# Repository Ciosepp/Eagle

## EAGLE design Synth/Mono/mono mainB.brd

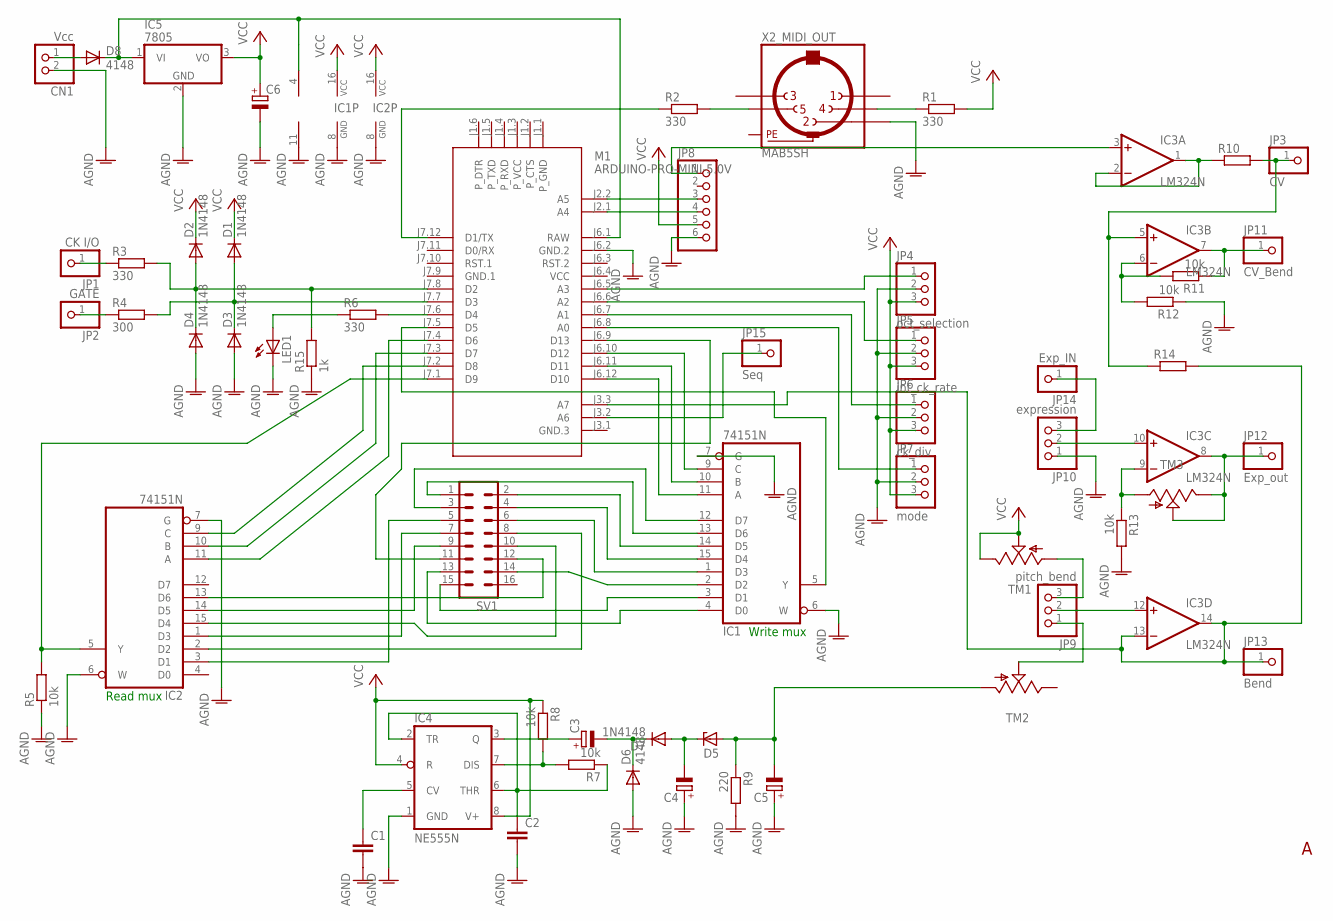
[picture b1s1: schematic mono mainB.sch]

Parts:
C1, C2: C-EU050-025X075; C050-025X075
C3, C4, C5, C6: CPOL-EUE5-8.5; E5-8,5
CN1: Vcc; JST-PH-2-THM
D1, D2, D3, D4, D7: 1N4148; DO35-7
D5: ZENER-DIODEZD-7.5; ZDIO-7.5
D6, D8: 4148; DO35-7
IC1, IC2: 74151N; DIL16
IC3: LM324N; DIL14
IC4: NE555N; DIL08-ROUND
IC5: 7805; TO220V
JP1: CK I/O; 1X01
JP2: GATE; 1X01
JP3: CV; 1X01
JP4: oct_selection; 1X03
JP5: int_ck_rate; 1X03
JP6: ck_div; 1X03
JP7: mode; 1X03
JP8: PINHD-1X6; 1X06
JP9: pitch_bend; 1X03
JP10: expression; 1X03
JP11: CV_Bend; 1X01
JP12: Exp_out; 1X01
JP13: Bend; 1X01
JP14: Exp_IN; 1X01
JP15: Seq; 1X01
LED1: LED5MM
M1: ARDUINO-PRO-MINI-5.0V; ARDUINO-PRO-MINI
R1: 330; 0204V
R2, R3: 330; 0204/7
R4: 300; 0204/7
R5: 10k; 0204/7
R6: 330; 0207/10
R7, R8, R11: 10k; 0204V
R9: 220; 0204V
R10, R14: R0204/7; 0204/7
R12, R13: 10k; 0207/10
R15: 1k; 0204/7
SV1: MA08-2
TM1, TM2, TM3: TRIM; 6MM
X2_MIDI_OUT: MAB5SH

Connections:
AGND: C1.2, C2.2, C4.+, C5.+, C6.-, CN1.2 (1), D3.A, D4.A, D6.A, IC1.6 (W), IC1.7 (G), IC1.8 (GND), IC2.6 (W), IC2.7 (G), IC2.8 (GND), IC3.11 (V-), IC4.1 (GND), IC5.2 (GND), JP4.2, JP5.2, JP6.2, JP7.2, JP8.6, JP10.1, LED1.K (C), M1.J6.2 (GND.2), R5.1, R9.2, R12.1, R13.2, R15.1, X2_MIDI_OUT.2
GND.1: M1.J7.9 (GND.1)
unnamed: IC1.12 (D7), SV1.3
unnamed: IC1.13 (D6), SV1.1
unnamed: IC1.14 (D5), SV1.2
unnamed: IC1.15 (D4), SV1.4
unnamed: IC1.1 (D3), SV1.6
unnamed: IC1.4 (D0), SV1.13
unnamed: IC1.2 (D2), SV1.14
unnamed: IC1.3 (D1), SV1.15
unnamed: IC2.13 (D6), SV1.12
unnamed: IC2.14 (D5), SV1.9
unnamed: IC2.15 (D4), SV1.10
unnamed: IC2.1 (D3), SV1.7
unnamed: IC2.2 (D2), SV1.8
unnamed: JP1.1, R3.1
unnamed: IC1.11 (A), M1.J6.12 (D10)
unnamed: IC1.10 (B), M1.J6.11 (D11)
unnamed: M1.J7.12 (D1/TX), R2.1
unnamed: IC2.3 (D1), SV1.5
unnamed: JP8.3, M1.J2.2 (A5)
unnamed: D2.A, D4.C, M1.J7.8 (D2), R3.2, R15.2
unnamed: D1.A, D3.C, M1.J7.7 (D3), R4.2
unnamed: IC2.5 (Y), M1.J7.1 (D9), R5.2
unnamed: IC1.5 (Y), M1.J7.5 (D5)
unnamed: JP6.1, M1.J6.7 (A1)
unnamed: JP5.1, M1.J6.6 (A2)
unnamed: JP2.1, R4.1
unnamed: JP8.4, M1.J2.1 (A4)
unnamed: R2.2, X2_MIDI_OUT.5
unnamed: R1.1, X2_MIDI_OUT.4
unnamed: IC3.9 (-IN), R13.1, TM3.A
unnamed: JP4.1, M1.J6.5 (A3)
unnamed: IC2.9 (C), M1.J7.2 (D8)
unnamed: IC2.10 (B), M1.J7.3 (D7)
unnamed: IC2.11 (A), M1.J7.4 (D6)
unnamed: LED1.A, R6.1
unnamed: M1.J7.6 (D4), R6.2
unnamed: IC4.7 (DIS), R7.2, R8.2
unnamed: C2.1, IC4.2 (TR), IC4.6 (THR), R7.1
unnamed: C1.1, IC4.5 (CV)
unnamed: IC3.1 (OUT), IC3.2 (-IN), R10.1
unnamed: C3.+, IC4.3 (Q)
unnamed: C3.-, D6.C, D7.C
unnamed: C4.-, D5.C, D7.A
unnamed: C5.-, D5.A, R9.1, TM2.A
unnamed: IC3.12 (+IN), JP9.2
unnamed: IC3.13 (-IN), IC3.14 (OUT), JP13.1, M1.J3.3 (A7), R14.2
unnamed: JP9.3, TM1.A
unnamed: IC3.10 (+IN), JP10.2
unnamed: IC3.8 (OUT), JP12.1, TM3.E, TM3.S
unnamed: CN1.1 (2), D8.A
unnamed: JP9.1, TM2.S
unnamed: IC3.6 (-IN), R11.2, R12.2
unnamed: IC3.7 (OUT), JP11.1, R11.1
unnamed: D8.C, IC3.4 (V+), IC5.1 (VI), M1.J6.1 (RAW)
unnamed: IC1.9 (C), M1.J6.10 (D12)
unnamed: IC3.3 (+IN), JP8.1
unnamed: IC3.5 (+IN), JP3.1, R10.2, R14.1
unnamed: JP10.3, JP14.1
unnamed: M1.J6.9 (D13), SV1.11
unnamed: JP7.1, M1.J6.8 (A0)
unnamed: JP15.1, M1.J3.2 (A6)
PE: X2_MIDI_OUT.PE, X2_MIDI_OUT.PE@ (PE)
VCC: C6.+, D1.C, D2.C, IC1.16 (VCC), IC2.16 (VCC), IC4.4 (R), IC4.8 (V+), IC5.3 (VO), JP4.3, JP5.3, JP6.3, JP7.3, JP8.5, M1.J6.4 (VCC), R1.2, R8.1, TM1.E, TM1.S

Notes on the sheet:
Read mux
Write mux

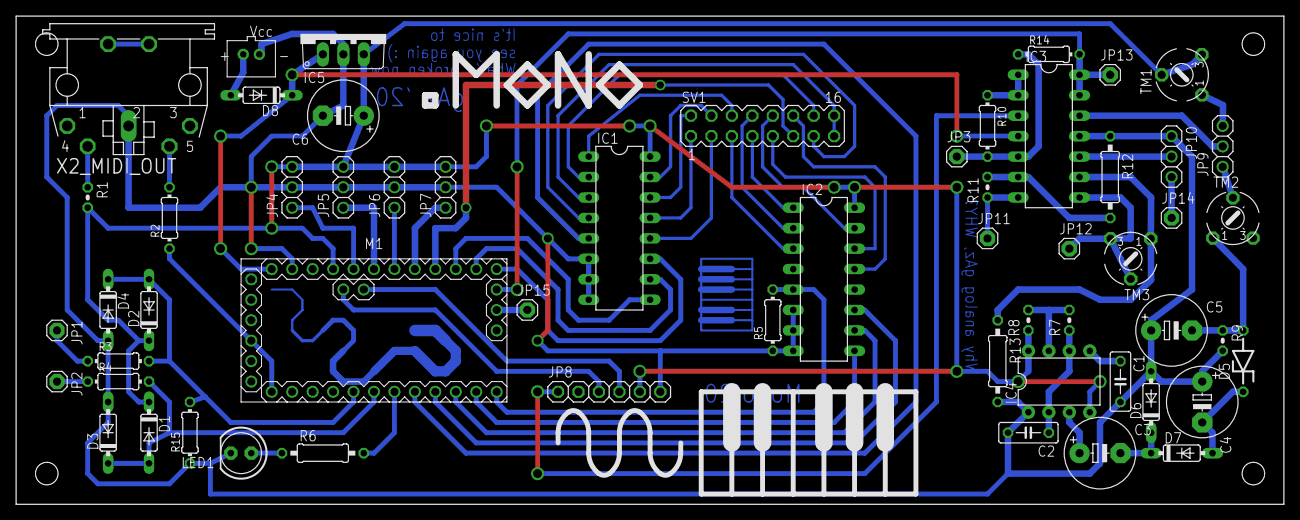
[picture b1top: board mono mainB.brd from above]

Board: 2 copper layers, 157.5 x 60.6 mm, 57 parts (0 on the bottom side), 64 nets.

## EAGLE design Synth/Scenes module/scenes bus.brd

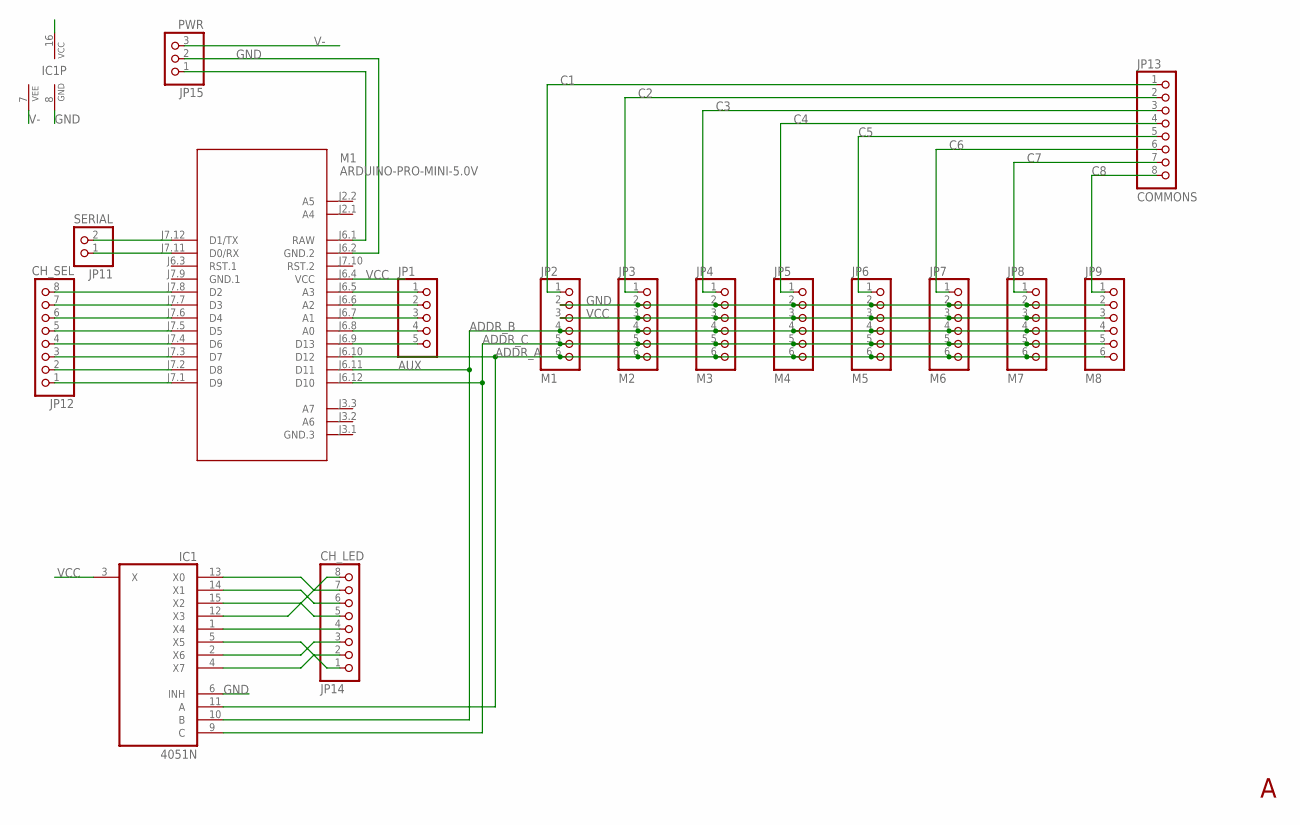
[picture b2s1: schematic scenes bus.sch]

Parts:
IC1: 4051N; DIL16
JP1: AUX; 1X05
JP2: M1; 1X06
JP3: M2; 1X06
JP4: M3; 1X06
JP5: M4; 1X06
JP6: M5; 1X06
JP7: M6; 1X06
JP8: M7; 1X06
JP9: M8; 1X06
JP11: SERIAL; 1X02
JP12: CH_SEL; 1X08
JP13: COMMONS; 1X08
JP14: CH_LED; 1X08
JP15: PWR; 1X03
M1: ARDUINO-PRO-MINI-5.0V; ARDUINO-PRO-MINI#NP

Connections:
ADDR_A: IC1.11 (A), JP2.6, JP3.6, JP4.6, JP5.6, JP6.6, JP7.6, JP8.6, JP9.6, M1.J6.10 (D12)
ADDR_B: IC1.10 (B), JP2.4, JP3.4, JP4.4, JP5.4, JP6.4, JP7.4, JP8.4, JP9.4, M1.J6.11 (D11)
ADDR_C: IC1.9 (C), JP2.5, JP3.5, JP4.5, JP5.5, JP6.5, JP7.5, JP8.5, JP9.5, M1.J6.12 (D10)
C1: JP2.1, JP13.1
C2: JP3.1, JP13.2
C3: JP4.1, JP13.3
C4: JP5.1, JP13.4
C5: JP6.1, JP13.5
C6: JP7.1, JP13.6
C7: JP8.1, JP13.7
C8: JP9.1, JP13.8
GND: IC1.6 (INH), IC1.8 (GND), JP2.2, JP3.2, JP4.2, JP5.2, JP6.2, JP7.2, JP8.2, JP9.2, JP15.2, M1.J6.2 (GND.2)
GND.1: M1.J7.9 (GND.1)
unnamed: JP1.1, M1.J6.5 (A3)
unnamed: JP1.2, M1.J6.6 (A2)
unnamed: JP1.3, M1.J6.7 (A1)
unnamed: JP1.4, M1.J6.8 (A0)
unnamed: JP1.5, M1.J6.9 (D13)
unnamed: JP12.1, M1.J7.1 (D9)
unnamed: JP12.2, M1.J7.2 (D8)
unnamed: JP12.3, M1.J7.3 (D7)
unnamed: JP12.4, M1.J7.4 (D6)
unnamed: JP12.5, M1.J7.5 (D5)
unnamed: JP12.6, M1.J7.6 (D4)
unnamed: JP12.7, M1.J7.7 (D3)
unnamed: JP12.8, M1.J7.8 (D2)
unnamed: IC1.1 (X4), JP14.4
unnamed: IC1.2 (X6), JP14.3
unnamed: JP11.2, M1.J7.12 (D1/TX)
unnamed: JP11.1, M1.J7.11 (D0/RX)
unnamed: IC1.4 (X7), JP14.2
unnamed: IC1.5 (X5), JP14.1
unnamed: JP15.1, M1.J6.1 (RAW)
unnamed: IC1.15 (X2), JP14.5
unnamed: IC1.14 (X1), JP14.6
unnamed: IC1.13 (X0), JP14.7
unnamed: IC1.12 (X3), JP14.8
V-: IC1.7 (VEE), JP15.3
VCC: IC1.3 (X), IC1.16 (VCC), JP2.3, JP3.3, JP4.3, JP5.3, JP6.3, JP7.3, JP8.3, JP9.3, M1.J6.4 (VCC)

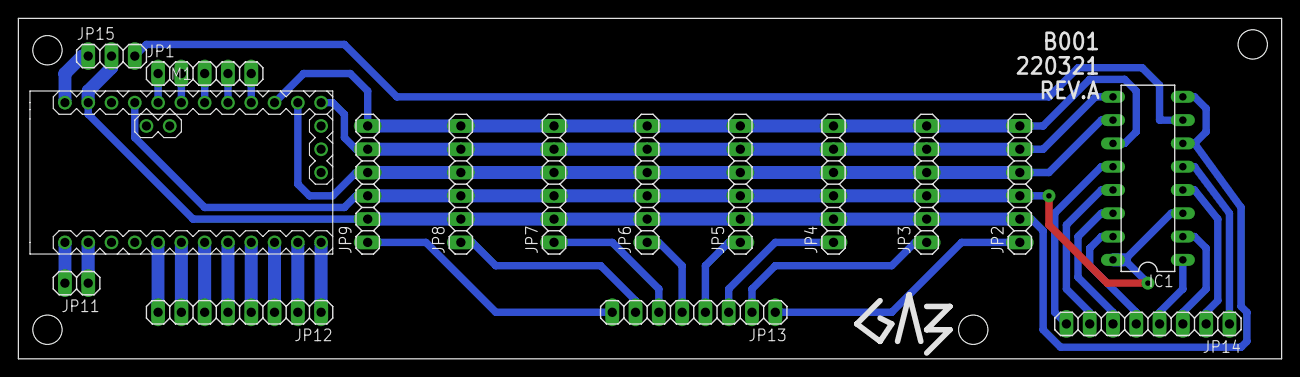
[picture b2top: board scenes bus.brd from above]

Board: 2 copper layers, 137.8 x 37.1 mm, 16 parts (0 on the bottom side), 38 nets.

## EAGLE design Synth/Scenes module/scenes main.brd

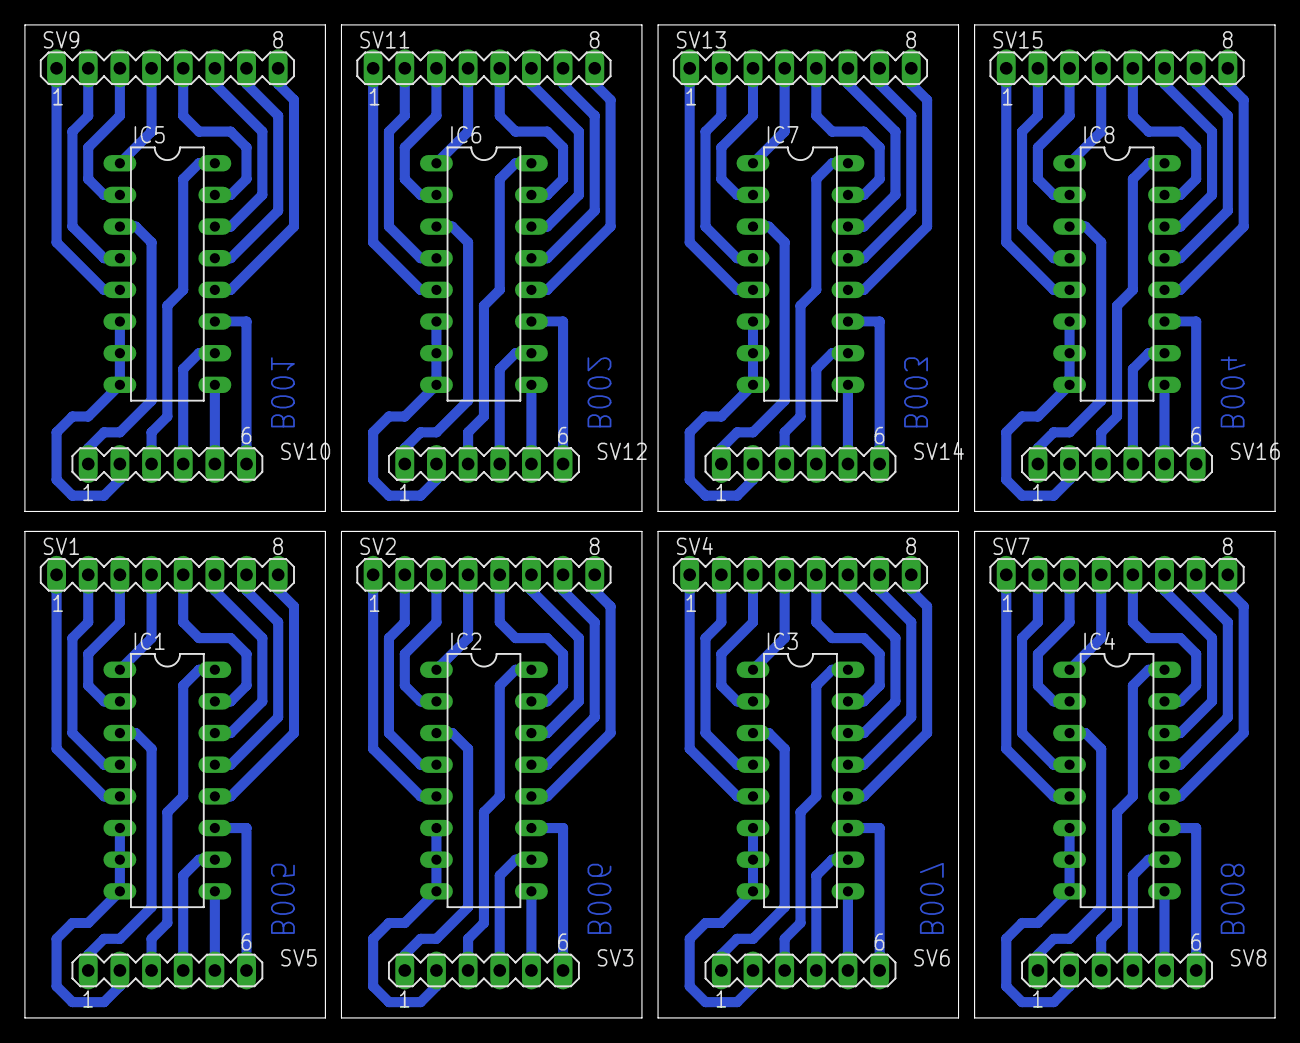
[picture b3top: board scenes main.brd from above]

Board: 2 copper layers, 100.3 x 79.7 mm, 24 parts (0 on the bottom side), 112 nets.

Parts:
IC1, IC2, IC3, IC4, IC5, IC6, IC7, IC8: 4051N; DIL16
SV1, SV2, SV4, SV7, SV9, SV11, SV13, SV15: MA08-1
SV3, SV5, SV6, SV8, SV10, SV12, SV14, SV16: MA06-1

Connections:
GND: IC1.6, IC1.8, SV5.2
GND1: IC2.6, IC2.8, SV3.2
GND2: IC3.6, IC3.8, SV6.2
GND3: IC4.6, IC4.8, SV8.2
GND4: IC5.6, IC5.8, SV10.2
GND5: IC6.6, IC6.8, SV12.2
GND6: IC7.6, IC7.8, SV14.2
GND7: IC8.6, IC8.8, SV16.2
unnamed: IC1.1, SV1.4
unnamed: IC1.2, SV1.3
unnamed: IC1.4, SV1.2
unnamed: IC1.5, SV1.1
unnamed: IC1.15, SV1.5
unnamed: IC1.14, SV1.6
unnamed: IC1.13, SV1.7
unnamed: IC1.12, SV1.8
unnamed: IC1.9, SV5.5
unnamed: IC1.10, SV5.4
unnamed: IC1.11, SV5.6
unnamed: IC2.1, SV2.4
unnamed: IC2.2, SV2.3
unnamed: IC2.4, SV2.2
unnamed: IC2.5, SV2.1
unnamed: IC2.15, SV2.5
unnamed: IC2.14, SV2.6
unnamed: IC2.13, SV2.7
unnamed: IC2.12, SV2.8
unnamed: IC2.3, SV3.1
unnamed: IC2.9, SV3.5
unnamed: IC2.10, SV3.4
unnamed: IC2.11, SV3.6
unnamed: IC3.1, SV4.4
unnamed: IC3.2, SV4.3
unnamed: IC3.4, SV4.2
unnamed: IC3.5, SV4.1
unnamed: IC3.15, SV4.5
unnamed: IC3.14, SV4.6
unnamed: IC3.13, SV4.7
unnamed: IC3.12, SV4.8
unnamed: IC3.3, SV6.1
unnamed: IC3.9, SV6.5
unnamed: IC3.10, SV6.4
unnamed: IC3.11, SV6.6
unnamed: IC4.1, SV7.4
unnamed: IC4.2, SV7.3
unnamed: IC4.4, SV7.2
unnamed: IC4.5, SV7.1
unnamed: IC4.15, SV7.5
unnamed: IC4.14, SV7.6
unnamed: IC4.13, SV7.7
unnamed: IC4.12, SV7.8
unnamed: IC4.3, SV8.1
unnamed: IC4.9, SV8.5
unnamed: IC4.10, SV8.4
unnamed: IC4.11, SV8.6
unnamed: IC5.1, SV9.4
unnamed: IC5.2, SV9.3
unnamed: IC5.4, SV9.2
unnamed: IC5.5, SV9.1
unnamed: IC5.15, SV9.5
unnamed: IC5.14, SV9.6
unnamed: IC5.13, SV9.7
unnamed: IC5.12, SV9.8
unnamed: IC5.3, SV10.1
unnamed: IC5.9, SV10.5
unnamed: IC5.10, SV10.4
unnamed: IC5.11, SV10.6
unnamed: IC6.1, SV11.4
unnamed: IC6.2, SV11.3
unnamed: IC6.4, SV11.2
unnamed: IC6.5, SV11.1
unnamed: IC6.15, SV11.5
unnamed: IC6.14, SV11.6
unnamed: IC6.13, SV11.7
unnamed: IC6.12, SV11.8
unnamed: IC6.3, SV12.1
unnamed: IC6.9, SV12.5
unnamed: IC6.10, SV12.4
unnamed: IC6.11, SV12.6
unnamed: IC7.1, SV13.4
unnamed: IC7.2, SV13.3
unnamed: IC7.4, SV13.2
unnamed: IC1.3, SV5.1
unnamed: IC7.5, SV13.1
unnamed: IC7.15, SV13.5
unnamed: IC7.14, SV13.6
unnamed: IC7.13, SV13.7
unnamed: IC7.12, SV13.8
unnamed: IC7.3, SV14.1
unnamed: IC7.9, SV14.5
unnamed: IC7.10, SV14.4
unnamed: IC7.11, SV14.6
unnamed: IC8.1, SV15.4
unnamed: IC8.2, SV15.3
unnamed: IC8.4, SV15.2
unnamed: IC8.5, SV15.1
unnamed: IC8.15, SV15.5
unnamed: IC8.14, SV15.6
unnamed: IC8.13, SV15.7
unnamed: IC8.12, SV15.8
unnamed: IC8.3, SV16.1
unnamed: IC8.9, SV16.5
unnamed: IC8.10, SV16.4
unnamed: IC8.11, SV16.6
VCC: IC1.16, SV5.3
VCC1: IC2.16, SV3.3
VCC2: IC3.16, SV6.3
VCC3: IC4.16, SV8.3
VCC4: IC5.16, SV10.3
VCC5: IC6.16, SV12.3
VCC6: IC7.16, SV14.3
VCC7: IC8.16, SV16.3

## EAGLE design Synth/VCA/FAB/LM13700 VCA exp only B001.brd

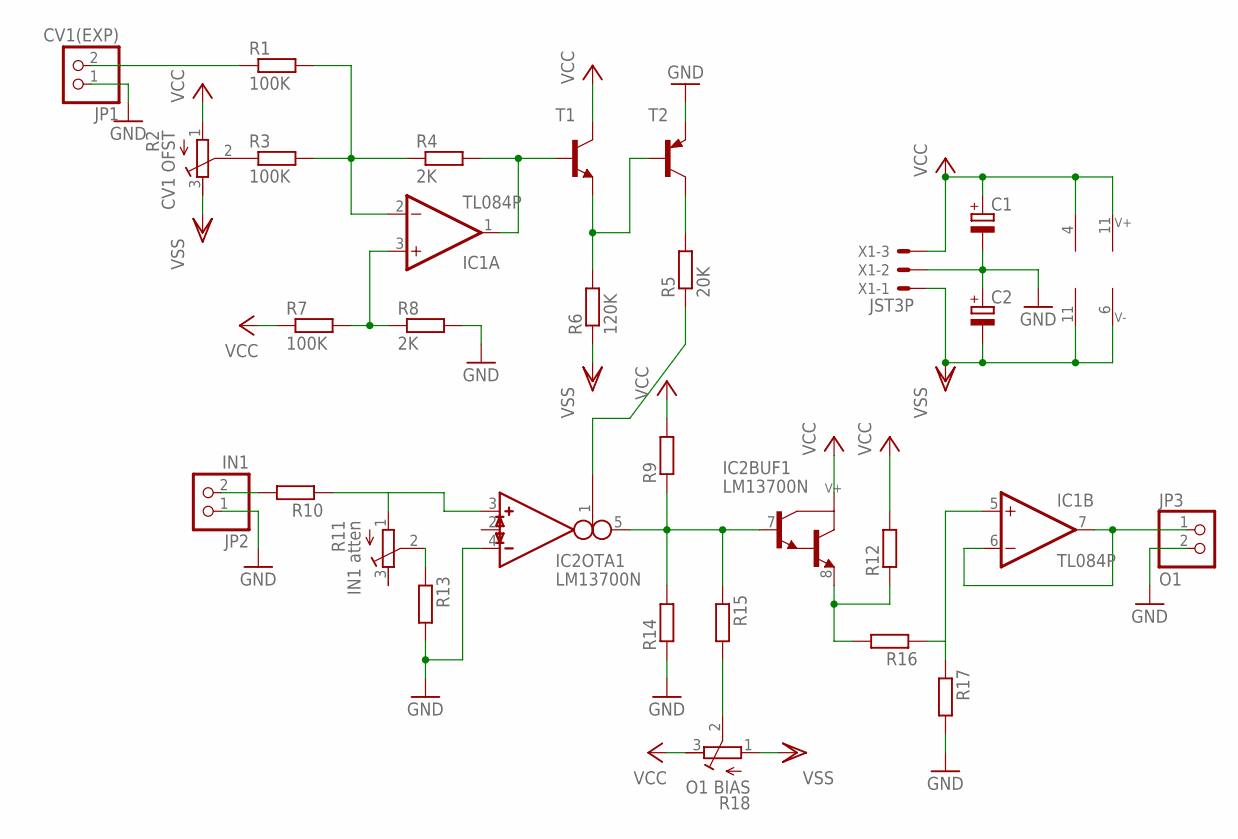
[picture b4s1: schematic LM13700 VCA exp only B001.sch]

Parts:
C1, C2: CPOL-EUE2.5-7; E2,5-7
IC1: TL084P; DIL14
IC2: LM13700N; DIL16
JP1: CV1(EXP); 1X02
JP2: IN1; 1X02
JP3: O1; 1X02
R1: 100K; 0204V
R2: CV1 OFST; RTRIM64W
R3, R7: 100K; 0204/7
R4: 2K; 0204V
R5: 20K; 0204/7
R6: 120K; 0204/7
R8: 2K; 0204/7
R9, R17: R-EU_0204/5; 0204/5
R10, R13, R14: R-EU_0204/2V; 0204V
R11: IN1 atten; RTRIM64W
R12, R15, R16: R-EU_0204/7; 0204/7
R18: O1 BIAS; RTRIM64W
T1: 2N3904-NPN-TO92-EBC; TO92-EBC
T2: 2N3906-PNP-TO92-EBC; TO92-EBC
X1: JST3P; JST-XH-03-PACKAGE-LONG-PAD

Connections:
GND: C1.-, C2.+, IC2.4 (IN_N), JP1.1, JP2.1, JP3.2, R8.2, R13.2, R14.1, R17.2, T2.E, X1.2
unnamed: IC1.3 (+IN), R7.2, R8.1
unnamed: IC1.2 (-IN), R1.2, R3.2, R4.1
unnamed: IC1.1 (OUT), R4.2, T1.B
unnamed: R6.2, T1.E, T2.B
unnamed: R5.2, T2.C
unnamed: JP1.2, R1.1
unnamed: R2.2 (S), R3.1
unnamed: IC2.1 (I_BIAS), R5.1
unnamed: IC2.3 (IN_P), R10.1, R11.1 (A)
unnamed: IC2.5 (OUT), IC2.7 (B), R9.1, R14.2, R15.1
unnamed: R15.2, R18.2 (S)
unnamed: IC2.8 (E), R12.1, R16.2
unnamed: IC1.5 (+IN), R16.1, R17.1
unnamed: IC1.6 (-IN), IC1.7 (OUT), JP3.1
unnamed: JP2.2, R10.2
unnamed: R11.2 (S), R13.1
V-: C2.-, IC1.11 (V-), IC2.6 (V-), X1.1
VCC: C1.+, IC1.4 (V+), IC2.11 (V+), R2.1 (A), R7.1, R9.2, R12.2, R18.3 (E), T1.C, X1.3
VSS: R2.3 (E), R6.1, R18.1 (A)

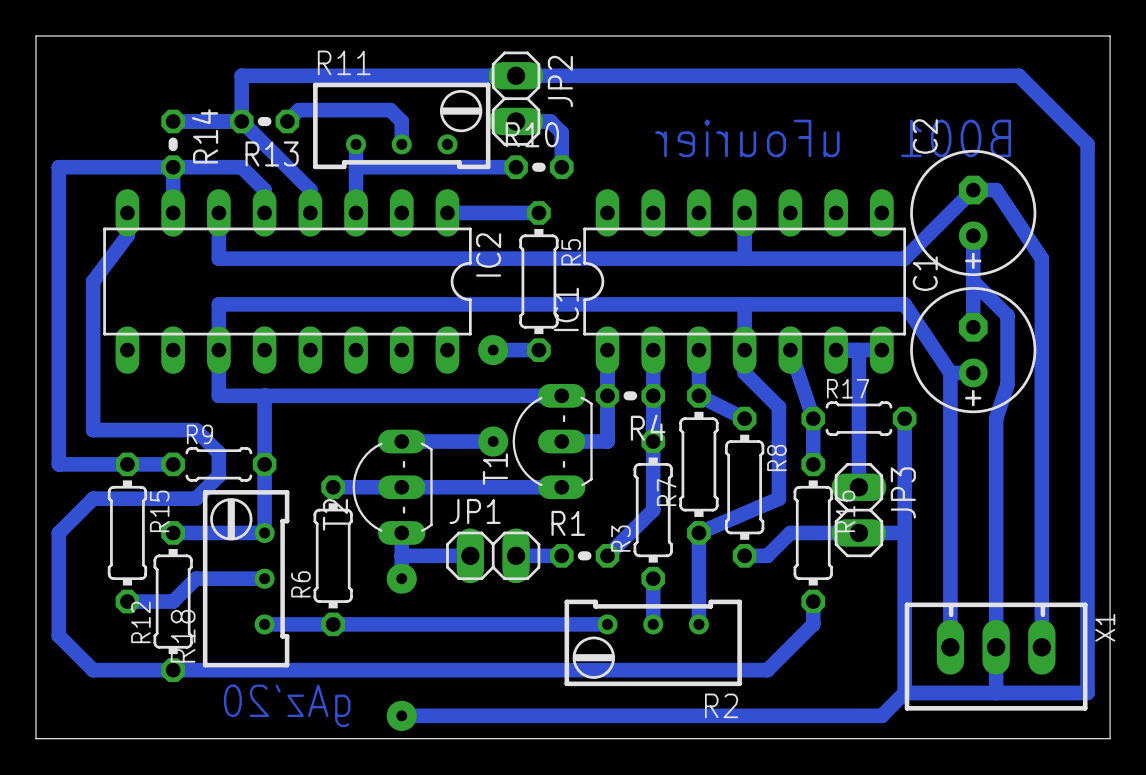
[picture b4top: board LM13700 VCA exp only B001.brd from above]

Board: 2 copper layers, 59.7 x 39.0 mm, 28 parts (0 on the bottom side), 20 nets.

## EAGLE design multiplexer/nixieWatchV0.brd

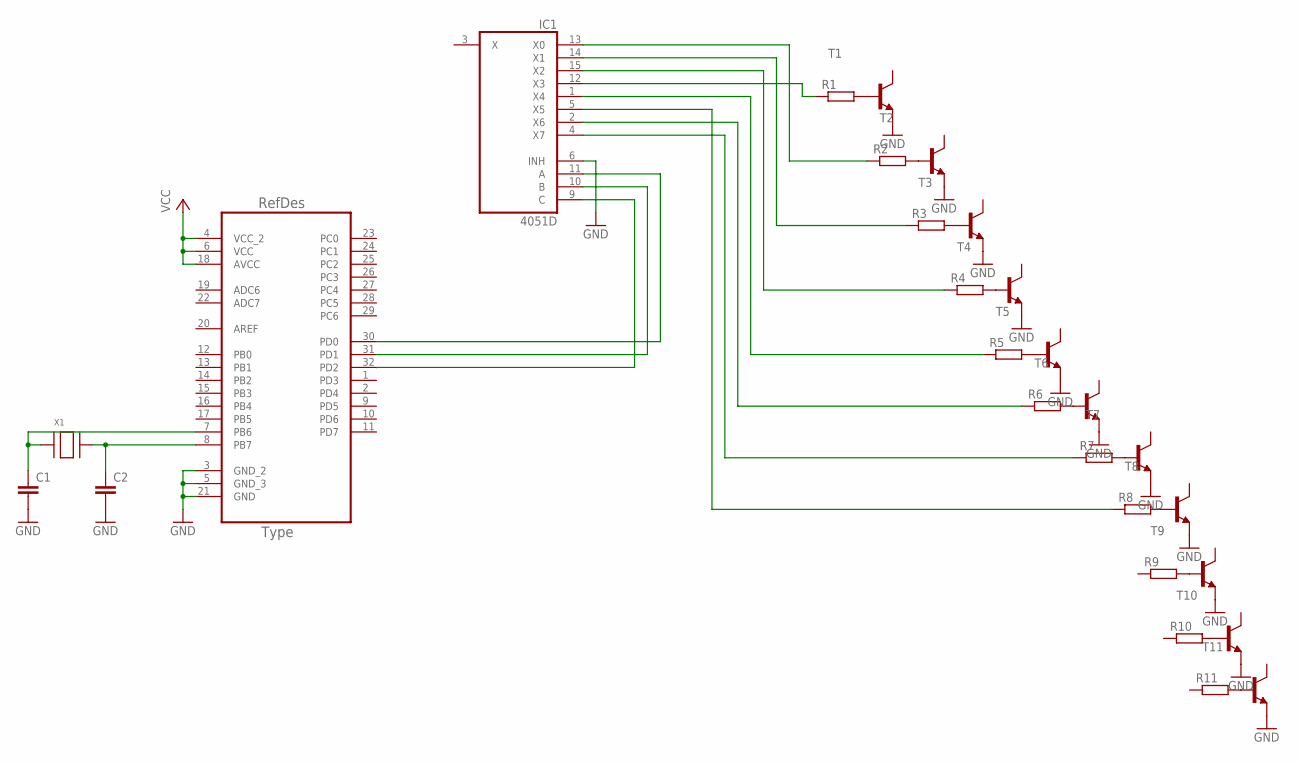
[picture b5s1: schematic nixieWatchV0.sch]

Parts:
C1, C2: C-EUC0402; C0402
IC1: 4051D; SO16
R1, R2, R3, R4, R5, R6, R7, R8, R9, R10, R11: R-EU_M1206; M1206
T1, T2, T3, T4, T5, T6, T7, T8, T9, T10, T11: -NPN-SOT23-EBC; SOT23-EBC
U1: ATMEGA328P-AU; QFP80P900X900X120-32N
X1: XTAL-3.2X1.5; XTAL3215

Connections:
GND: C1.2, C2.2, IC1.6 (INH), IC1.8 (GND), T1.E, T2.E, T3.E, T4.E, T5.E, T6.E, T7.E, T8.E, T9.E, T10.E, T11.E, U1.3 (GND_2), U1.5 (GND_3), U1.21 (GND)
unnamed: R1.2, T1.B
unnamed: R2.2, T2.B
unnamed: R3.2, T3.B
unnamed: R4.2, T4.B
unnamed: R5.2, T5.B
unnamed: R6.2, T6.B
unnamed: R7.2, T7.B
unnamed: R8.2, T8.B
unnamed: R9.2, T9.B
unnamed: R10.2, T10.B
unnamed: R11.2, T11.B
unnamed: IC1.12 (X3), R1.1
unnamed: C1.1, U1.7 (PB6), X1.P$1
unnamed: C2.1, U1.8 (PB7), X1.P$2
unnamed: IC1.13 (X0), R2.1
unnamed: IC1.14 (X1), R3.1
unnamed: IC1.15 (X2), R4.1
unnamed: IC1.1 (X4), R5.1
unnamed: IC1.2 (X6), R6.1
unnamed: IC1.4 (X7), R7.1
unnamed: IC1.10 (B), U1.31 (PD1)
unnamed: IC1.5 (X5), R8.1
unnamed: IC1.11 (A), U1.30 (PD0)
unnamed: IC1.9 (C), U1.32 (PD2)
VCC: IC1.16 (VCC), U1.4 (VCC_2), U1.6 (VCC), U1.18 (AVCC)
VEE: IC1.7 (VEE)

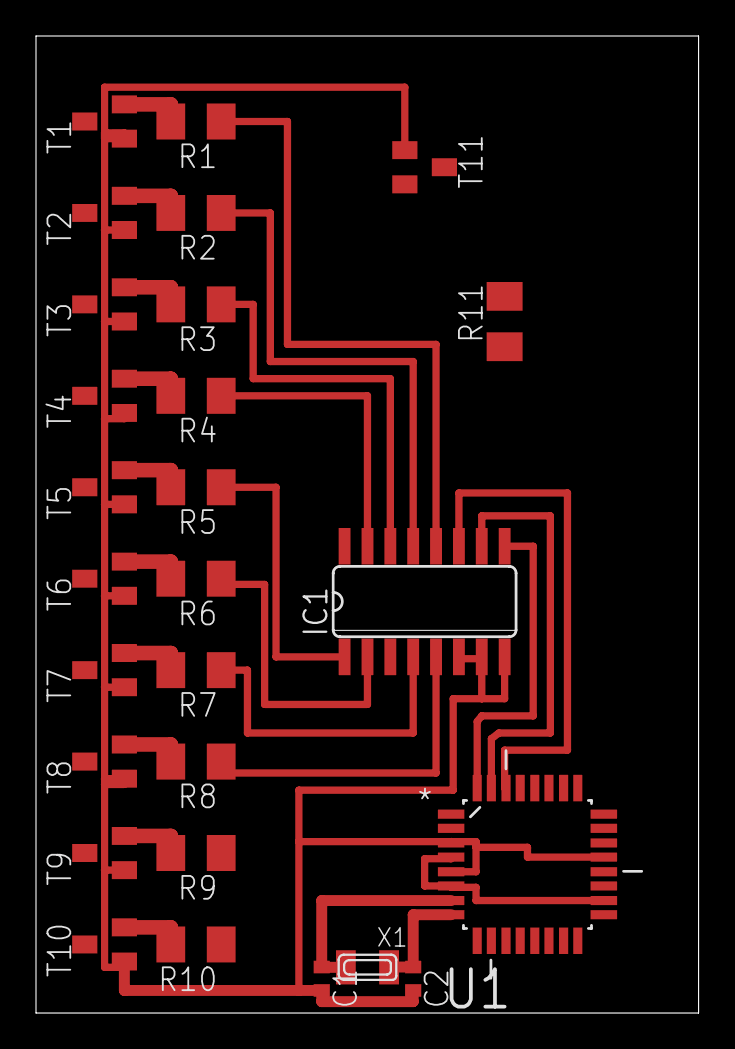
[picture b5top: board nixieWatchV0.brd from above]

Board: 2 copper layers, 36.8 x 54.3 mm, 27 parts (0 on the bottom side), 26 nets.

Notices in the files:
parts and their libraries:
diy-modules: Released under the Creative Commons Attribution 4.0 International License: http://creativecommons.org/licenses/by/4.0
